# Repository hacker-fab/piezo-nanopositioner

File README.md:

# piezo-nanopositioner

To install the ESP-IDF you should follow this guide for [Linux and macOS](https://docs.espressif.com/projects/esp-idf/en/v5.2.1/esp32s3/get-started/linux-macos-setup.html) and [Windows](https://docs.espressif.com/projects/esp-idf/en/v5.2.1/esp32s3/get-started/windows-setup.html). Once you have the ESP-IDF installed you will need to run the `export.sh` file located in `esp/esp-idf/export.sh` inside the `esp` folder you setup. Once you have setup ESP-IDF for your current terminal session, you can now run `idf.py build` to compile the code or `idf.py -p {serial port the device is connected to} flash`.

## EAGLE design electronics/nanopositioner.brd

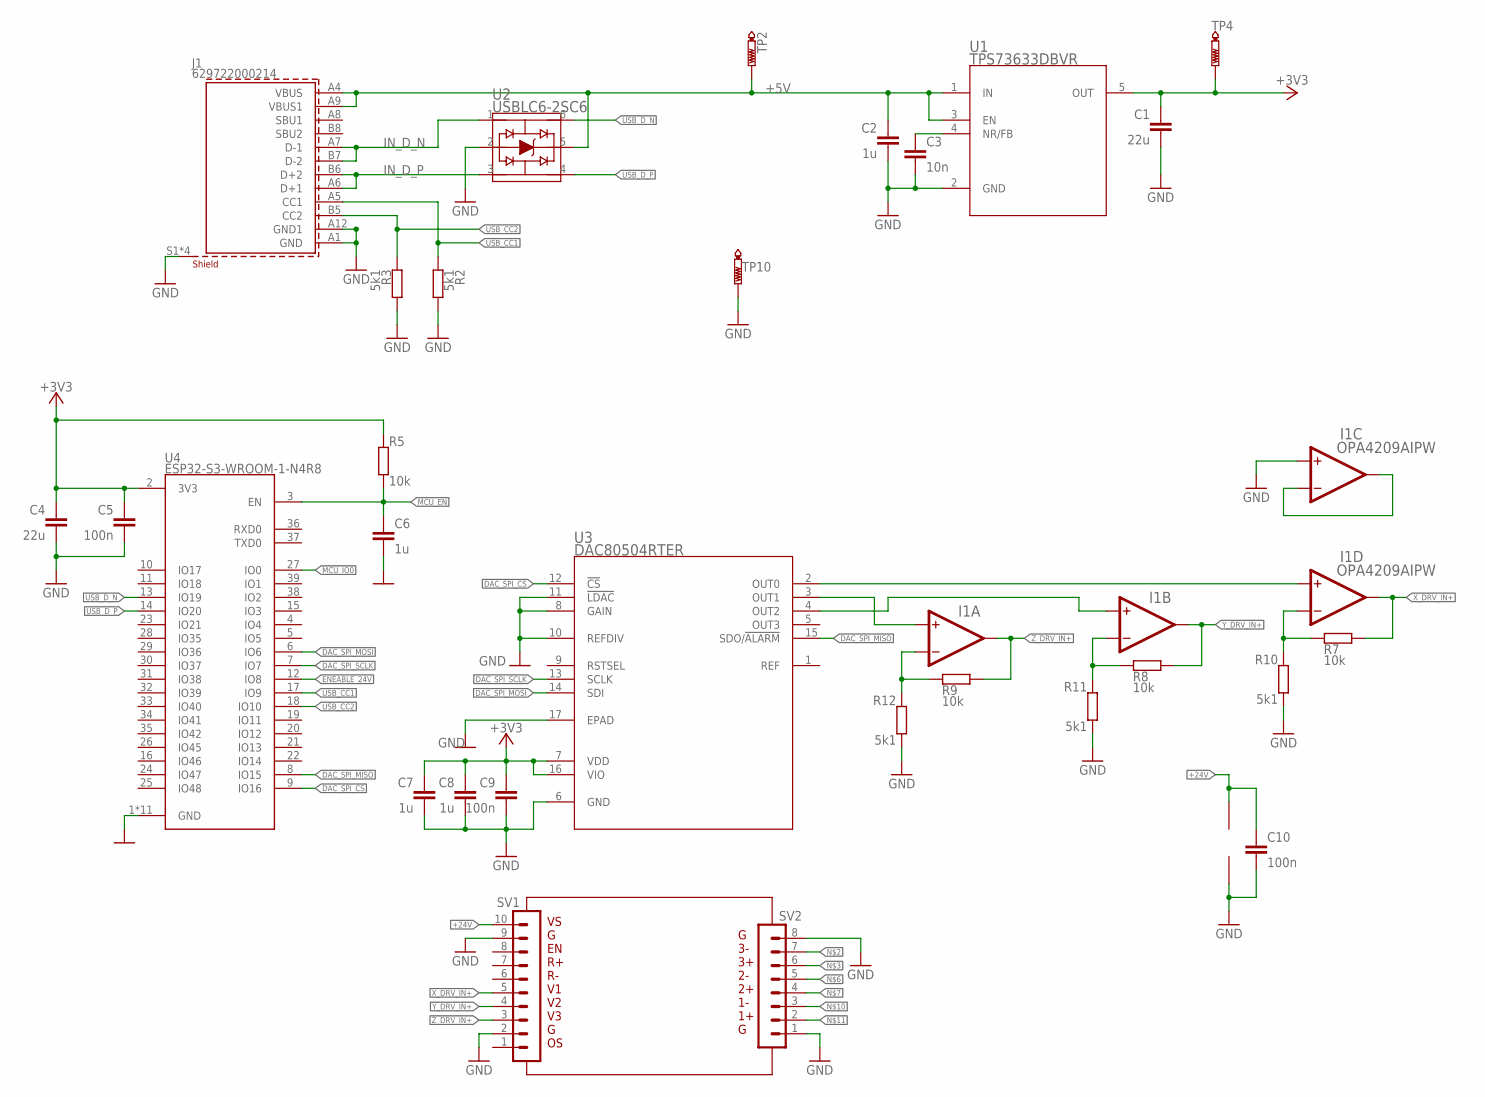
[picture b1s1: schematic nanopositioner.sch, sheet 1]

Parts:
C1, C4: 22u; C0603; MPN CL10A226MP8NUNE
C2, C6, C7, C8: 1u; C0402; MPN GRM155R61E105MA12D
C3: 10n; C0402; MPN GCM155R71H103KA55D
C5, C9, C10: 100n; C0402; MPN GRM155R71H104KE14D
I1: OPA4209AIPW; PW14; MPN OPA4209AIPW
J1: 629722000214; MPN 12402012E212A
R2, R3, R10, R11, R12: 5k1; R0402; MPN ERA-2AEB512X
R5, R7, R8, R9: 10k; R0402; MPN ERA-2AEB103X
SV1: MA10-1
SV2: MA08-1
TP2, TP4, TP10: PTR1PAD1-13; P1-13
U1: TPS73633DBVR; DBV5; MPN TPS73633DBVR
U2: USBLC6-2SC6; SOT23-6L_STM; MPN USBLC6-2SC6
U3: DAC80504RTER; RTE16_TEX; MPN DAC80504RTET
U4: ESP32-S3-WROOM-1-N4R8; XCVR_ESP32S3WROOM1N8R8; MPN ESP32-S3-WROOM-1-N4

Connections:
+3V3: C1.1, C4.1, C5.1, C7.1, C8.1, C9.1, R5.1, TP4.TP, U1.5 (OUT), U3.7 (VDD), U3.16 (VIO), U4.2 (3V3)
+5V: C2.2, J1.A4 (VBUS), J1.A9 (VBUS1), TP2.TP, U1.1 (IN), U1.3 (EN), U2.5; also elsewhere on the board
+24V: C10.1, I1.4, SV1.10; also elsewhere on the board
DAC_SPI_CS: U3.12 (!CS), U4.9 (IO16)
DAC_SPI_MISO: U3.15 (SDO/!ALARM), U4.8 (IO15)
DAC_SPI_MOSI: U3.14 (SDI), U4.6 (IO6)
DAC_SPI_SCLK: U3.13 (SCLK), U4.7 (IO7)
ENEABLE_24V: U4.12 (IO8); also elsewhere on the board
GND: C1.2, C2.1, C3.2, C4.2, C5.2, C6.1, C7.2, C8.2, C9.2, C10.2, I1.10 (INA+), I1.11, J1.A1 (GND), J1.A12 (GND1), J1.S1 (SHIELD), J1.S2 (SHIELD), J1.S3 (SHIELD), J1.S4 (SHIELD), R2.1, R3.2, R10.2, R11.2, R12.2, SV1.2, SV1.9, SV2.1, SV2.8, TP10.TP, U1.2 (GND), U2.2, U3.6 (GND), U3.8 (GAIN), U3.10 (REFDIV), U3.11 (!LDAC), U3.17 (EPAD), U4.1 (GND), U4.40 (GND), U4.41_1 (GND), U4.41_2 (GND), U4.41_3 (GND), U4.41_4 (GND), U4.41_5 (GND), U4.41_6 (GND), U4.41_7 (GND), U4.41_8 (GND), U4.41_9 (GND); also elsewhere on the board
IN_D_N: J1.A7 (D-1), J1.B7 (D-2), U2.1
IN_D_P: J1.A6 (D+1), J1.B6 (D+2), U2.3
MCU_EN: C6.2, R5.2, U4.3 (EN)
MCU_IO0: U4.27 (IO0)
unnamed: I1.13 (INA-), R7.1, R10.1
unnamed: C3.1, U1.4 (NR/FB)
unnamed: I1.3 (INA+), U3.3 (OUT1)
unnamed: I1.6 (INA-), R8.1, R11.1
unnamed: I1.5 (INA+), U3.4 (OUT2)
unnamed: I1.2 (INA-), R9.1, R12.1
unnamed: I1.12 (INA+), U3.2 (OUT0)
unnamed: I1.8 (OUTA), I1.9 (INA-)
USB_CC1: J1.A5 (CC1), R2.2, U4.17 (IO9)
USB_CC2: J1.B5 (CC2), R3.1, U4.18 (IO10)
USB_D_N: U2.6, U4.13 (IO19)
USB_D_P: U2.4, U4.14 (IO20)
X_DRV_IN+: I1.14 (OUTA), R7.2, SV1.5
Y_DRV_IN+: I1.7 (OUTA), R8.2, SV1.4
Z_DRV_IN+: I1.1 (OUTA), R9.2, SV1.3

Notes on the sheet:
VS G EN R+ R- V1 V2 V3 G OS
G 3- 3+ 2- 2+ 1- 1+ G

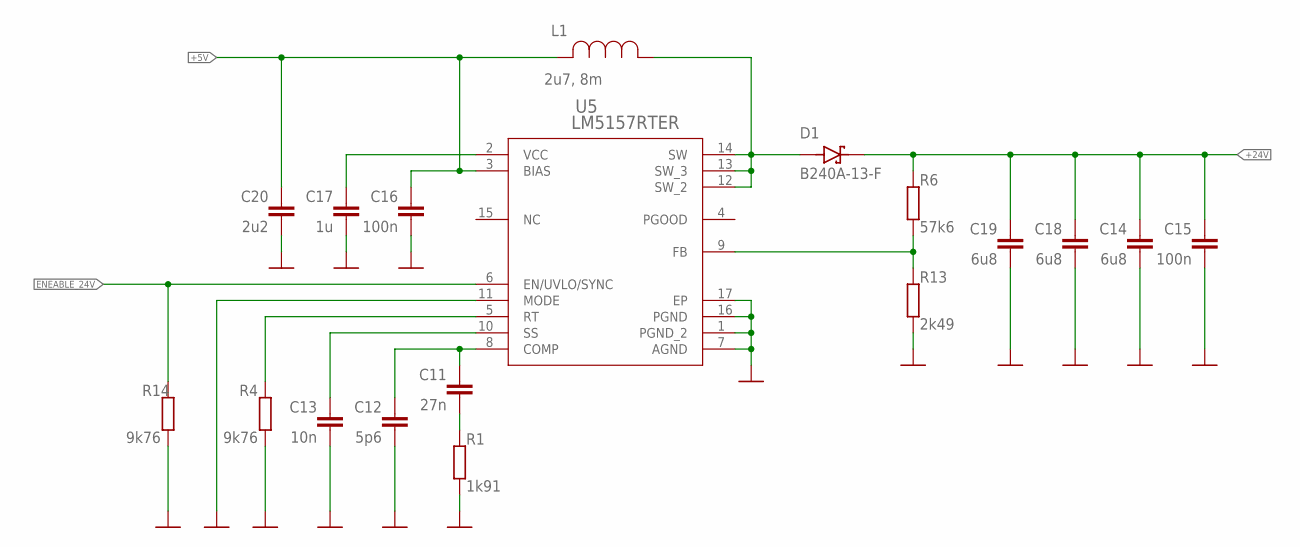
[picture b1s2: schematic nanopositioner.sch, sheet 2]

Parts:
C11: 27n; C0402; MPN GRM155R71A273KA01D
C12: 5p6; C0402; MPN GRM1555C1H5R6CA01D
C13: 10n; C0402; MPN GRM033R70J103KA01D
C14, C18, C19: 6u8; C1206; MPN C3216X5R1H685K160AB
C15: 100n; C0603; MPN CGA3E2X7R1H104K080AA
C16: 100n; C0603; MPN KGM21NR71E104KT
C17: 1u; C0402; MPN EMK107B7105KA-T
C20: 2u2; C0805; MPN GRM21BR71A225KA01L
D1: B240A-13-F; DIOM5226X230N; MPN B240A-13-F
L1: 2u7, 8m; IND_BOURNS_SDR1307; MPN SDR1307-2R7ML
R1: 1k91; R0402; MPN CRCW04021K91FKED
R4, R14: 9k76; R0402; MPN CRCW04029K76FKED
R6: 57k6; R0402; MPN CRCW040257K6FKED
R13: 2k49; R0402; MPN CRCW04022K49FKED
U5: LM5157RTER; QFN_57RTER_TEX; MPN LM5157RTER

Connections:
+5V: C16.2, C20.2, L1.2, U5.3 (BIAS); also elsewhere on the board
+24V: C14.2, C15.2, C18.2, C19.2, D1.C (K), R6.1; also elsewhere on the board
ENEABLE_24V: R14.1, U5.6 (EN/UVLO/SYNC); also elsewhere on the board
GND: C12.1, C13.1, C14.1, C15.1, C16.1, C17.1, C18.1, C19.1, C20.1, R1.2, R4.2, R13.2, R14.2, U5.1 (PGND_2), U5.7 (AGND), U5.11 (MODE), U5.16 (PGND), U5.17 (EP); also elsewhere on the board
unnamed: C11.2, C12.2, U5.8 (COMP)
unnamed: C11.1, R1.1
unnamed: C13.2, U5.10 (SS)
unnamed: R4.1, U5.5 (RT)
unnamed: D1.A, L1.1, U5.12 (SW_2), U5.13 (SW_3), U5.14 (SW)
unnamed: R6.2, R13.1, U5.9 (FB)
unnamed: C17.2, U5.2 (VCC)
PGOOD: U5.4 (PGOOD)

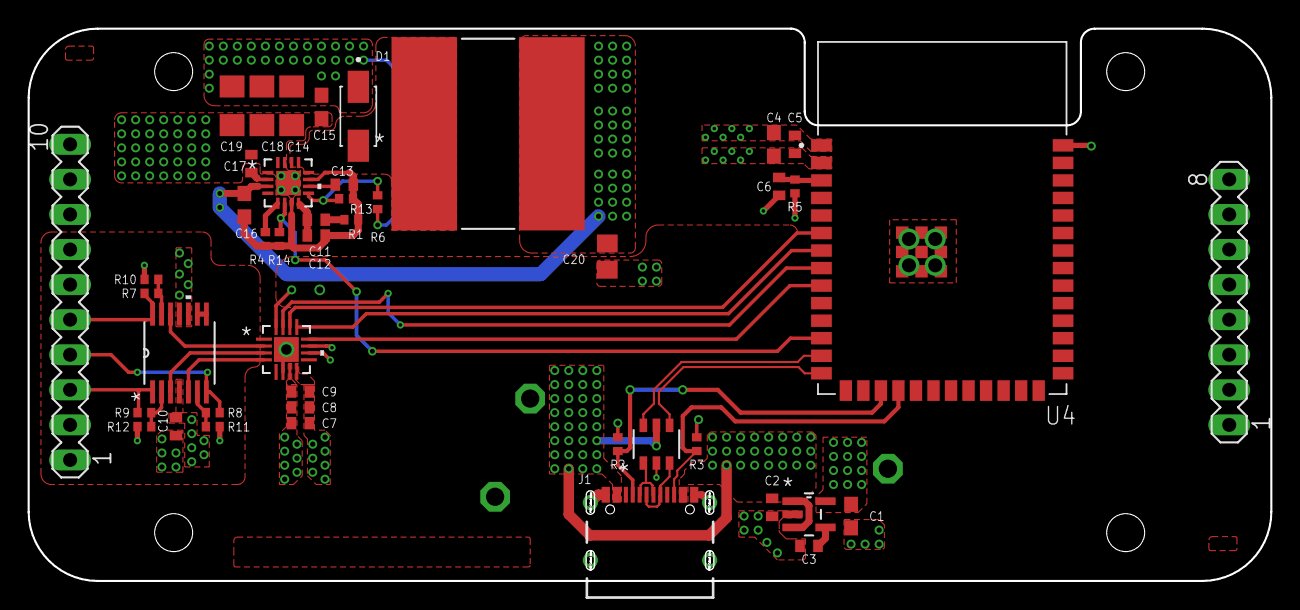
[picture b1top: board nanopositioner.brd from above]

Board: 4 copper layers, 90.0 x 40.0 mm, 48 parts (0 on the bottom side), 34 nets.

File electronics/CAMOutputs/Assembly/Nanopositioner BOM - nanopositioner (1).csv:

Qty,Designator,MPN,Description,Value,Footprint
1,SV2,,PIN HEADER,,MA08-1
1,SV1,,PIN HEADER,,MA10-1
3,"C5, C9, C10",GRM155R71H104KE14D,"CAPACITOR, European symbol",100n,C0402
1,C15,CGA3E2X7R1H104K080AA,"CAPACITOR, European symbol",100n,C0603
1,C16,KGM21NR71E104KT,"CAPACITOR, European symbol",100n,C0603
4,"R5, R7, R8, R9",ERA-2AEB103X,"RESISTOR, European symbol",10k,R0402
1,C3,GCM155R71H103KA55D,"CAPACITOR, European symbol",10n,C0402
1,C13,GRM033R70J103KA01D,"CAPACITOR, European symbol",10n,C0402
1,R1,CRCW04021K91FKED,"RESISTOR, European symbol",1k91,R0402
1,C17,EMK107B7105KA-T,"CAPACITOR, European symbol",1u,C0402
4,"C2, C6, C7, C8",GRM155R61E105MA12D,"CAPACITOR, European symbol",1u,C0402
2,"C1, C4",CL10A226MP8NUNE,"CAPACITOR, European symbol",22u,C0603
1,C11,GRM155R71A273KA01D,"CAPACITOR, European symbol",27n,C0402
1,R13,CRCW04022K49FKED,"RESISTOR, European symbol",2k49,R0402
1,C20,GRM21BR71A225KA01L,"CAPACITOR, European symbol",2u2,C0805
1,L1,SDR1307-2R7ML,,"2u7, 8m",IND_BOURNS_SDR1307
1,R6,CRCW040257K6FKED,"RESISTOR, European symbol",57k6,R0402
5,"R2, R3, R10, R11, R12",ERA-2AEB512X,"RESISTOR, European symbol",5k1,R0402
1,C12,GRM1555C1H5R6CA01D,"CAPACITOR, European symbol",5p6,C0402
1,J1,12402012E212A,WR-COM USB 2.0 Type C Plug Vertical SMT,629722000214,629722000214
3,"C14, C18, C19",C3216X5R1H685K160AB,"CAPACITOR, European symbol",6u8,C1206
2,"R4, R14",CRCW04029K76FKED,"RESISTOR, European symbol",9k76,R0402
1,D1,B240A-13-F,Diode Schottky 40V 2A Surface Mount SMA,B240A-13-F,DIOM5226X230N
1,U3,DAC80504RTET,,DAC80504RTER,RTE16_TEX
1,U4,ESP32-S3-WROOM-1-N4,Check availability  Check availability,ESP32-S3-WROOM-1-N4R8,XCVR_ESP32S3WROOM1N8R8
1,U5,LM5157RTER,,LM5157RTER,QFN_57RTER_TEX
1,I1,OPA4209AIPW,,OPA4209AIPW,PW14
3,"TP2, TP4, TP10",,TEST PIN,PTR1PAD1-13,P1-13
1,U1,TPS73633DBVR,,TPS73633DBVR,DBV5
1,U2,USBLC6-2SC6,,USBLC6-2SC6,SOT23-6L_STM

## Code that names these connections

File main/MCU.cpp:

#include "driver/spi_common.h"
#include "driver/spi_master.h"
#include "driver/uart.h"
#include "esp_err.h"
#include "esp_system.h"
#include "freertos/FreeRTOS.h"
#include "freertos/portmacro.h"
#include "freertos/task.h"
#include "driver/gpio.h"
#include "hal/gpio_types.h"
#include <stdint.h>
#include <sys/_stdint.h>
#include <sys/errno.h>
#include <sys/types.h>
#include <string.h>
#include <math.h>
#include <string>
#include "esp_timer.h"
#include "hal/usb_phy_types.h"
#include "tinyusb.h"
#include "tusb_cdc_acm.h"
#include "tusb_console.h"

const gpio_num_t ENEABLE_24V_PIN = GPIO_NUM_8;
const gpio_num_t DAC_SPI_MOSI = GPIO_NUM_6;
const gpio_num_t DAC_SPI_MISO = GPIO_NUM_15;
const gpio_num_t DAC_SPI_SCLK = GPIO_NUM_7;
const gpio_num_t DAC_SPI_CS = GPIO_NUM_16;

const int railCorrection = 12000;
const int maxADCValue = pow(2, 16)-1-railCorrection;

int g_itf;
int driveFrequency = 1000;
uint8_t transactionBuffer[CONFIG_TINYUSB_CDC_RX_BUFSIZE + 1] = {0};

int isDriverOn = 0;
int safeToRun = 1;
int running = 0;
spi_device_handle_t SPIDevice;

enum DACRegister : uint8_t {
	NOP = 0x00,
	DEVICEID = 0x01,
	SYNC = 0x02,
	CONFIG = 0x02,
	GAIN = 0x04,
	TRIGGER = 0x05,
	BRDCAST = 0x06,
	STATUS = 0x07,
	DAC0VAl = 0x08,
	DAC1VAl = 0x09,
	DAC2VAL = 0x0A,
	DAC3VAL = 0x0B,
};

enum DACChannel : uint8_t {
	DAC0 = 0,
	DAC1 = 1,
	DAC2 = 2,
	DAC3 = 3,
};

enum USBOpCode : uint32_t {
	ABORT = 0x74726261, // abrt
	RUN = 0x706E7572, // runp
	SETCH = 0x63746573, // setc
	SETFREQ = 0x66746573, // setf
};

void turnDriver(uint32_t on) {
	gpio_set_level(ENEABLE_24V_PIN, on);
}

void setupPins() {
	gpio_set_direction(ENEABLE_24V_PIN, GPIO_MODE_OUTPUT);
}

void initiateSPI(){

	spi_bus_config_t buscfg = {
		.mosi_io_num = DAC_SPI_MOSI,
		.miso_io_num = DAC_SPI_MISO,
		.sclk_io_num = DAC_SPI_SCLK,
		.max_transfer_sz = 4092,
	};

	spi_device_interface_config_t devcfg = {
		.command_bits = 0,
		.address_bits = 0,
		.dummy_bits = 0,
		.mode = 1,
		.clock_source = SPI_CLK_SRC_DEFAULT,
		.cs_ena_pretrans = 0,
		.cs_ena_posttrans = 0,
		.clock_speed_hz = SPI_MASTER_FREQ_40M,
		.spics_io_num = DAC_SPI_CS,
		.queue_size = 7,
	};

	esp_err_t ret;

	ret = spi_bus_initialize(SPI2_HOST, &buscfg, SPI_DMA_DISABLED);
	assert(ret==ESP_OK);

	ret = spi_bus_add_device(SPI2_HOST, &devcfg, &SPIDevice);
	assert(ret==ESP_OK);

	vTaskDelay(100 / portTICK_PERIOD_MS);
}

void writeToRegister(DACRegister address, uint16_t value)    {
	spi_device_acquire_bus(SPIDevice, portMAX_DELAY);
	spi_transaction_t transaction = {
		.flags = SPI_TRANS_USE_TXDATA,
		.length = 3*8,
	};

	transaction.tx_data[0] = (0b00000000 + (uint8_t)address);
	transaction.tx_data[1] = value >> 8;
	transaction.tx_data[2] = value;

	esp_err_t ret;
	ret = spi_device_transmit(SPIDevice, &transaction);
	assert(ret==ESP_OK);
	spi_device_release_bus(SPIDevice);
}

void fast_writeToRegister(DACRegister address, uint16_t value)    {
	spi_transaction_t transaction = {
		.flags = SPI_TRANS_USE_TXDATA,
		.length = 3*8,
	};

	transaction.tx_data[0] = (0b00000000 + (uint8_t)address);
	transaction.tx_data[1] = value >> 8;
	transaction.tx_data[2] = value;

	spi_device_polling_transmit(SPIDevice, &transaction);
}

void readFromRegister(DACRegister address, uint16_t &value){
	spi_device_acquire_bus(SPIDevice, portMAX_DELAY);
	uint8_t t_bytes[3];
	t_bytes[0] = (0b10000000 + (uint8_t)address);
	t_bytes[1] = 0;
	t_bytes[2] = 0;

	uint8_t r_bytes[3];
	memset(r_bytes, 0, sizeof(r_bytes));

	spi_transaction_t transaction = {
		.length = sizeof(t_bytes)*8,    // length in bits
		.tx_buffer = t_bytes,
		.rx_buffer = r_bytes
	};

	esp_err_t ret;
	ret = spi_device_transmit(SPIDevice, &transaction);
	assert(ret==ESP_OK);

	memset(r_bytes, 0, sizeof(r_bytes));

	transaction = {
		.length = sizeof(r_bytes)*8,    // length in bits
		.tx_buffer = r_bytes,
		.rx_buffer = r_bytes
	};

	ret = spi_device_transmit(SPIDevice, &transaction);
	assert(ret==ESP_OK);

	value = (uint16_t)(r_bytes[1] << 8 | r_bytes[2]);
	spi_device_release_bus(SPIDevice);
}

void setChannelBroadcast(DACChannel channel, int broadcast) {
	uint16_t registerValue = 0;
	readFromRegister(DACRegister::SYNC, registerValue);

	if(broadcast)
		writeToRegister(DACRegister::SYNC, registerValue | (1 << (8+channel)));
	else
		writeToRegister(DACRegister::SYNC, registerValue & (1 << (8+channel)));
}

void broadcast(uint16_t value) {
	writeToRegister(DACRegister::BRDCAST, value);
}

void fast_broadcast(uint16_t value) {
	fast_writeToRegister(DACRegister::BRDCAST, value+railCorrection);
}

long map(long x, long in_min, long in_max, long out_min, long out_max) {
    return (x - in_min) * (out_max - out_min) / (in_max - in_min) + out_min;
}

void stickSlip(int frequency, int direction) {
  long usPeriod = 1000000 / frequency;
  uint64_t usStart = esp_timer_get_time();
	uint64_t now = esp_timer_get_time();

	fast_broadcast(direction ? 0 : maxADCValue);

  while (1) {
		now = esp_timer_get_time();
		if (now - usStart > usPeriod) break;
		if (!safeToRun) return;

		if (direction == 1) {
			fast_broadcast((double)maxADCValue * pow((double)(now - usStart) / (double)usPeriod, 2));
		} else {
			fast_broadcast(maxADCValue - (double)maxADCValue * pow((double)(now - usStart) / (double)usPeriod, 2));
		}
	}

	fast_broadcast(0);
}

void initiateDAC() {
	setChannelBroadcast(DACChannel::DAC0, 0);
	setChannelBroadcast(DACChannel::DAC1, 0);
	setChannelBroadcast(DACChannel::DAC2, 0);
	setChannelBroadcast(DACChannel::DAC3, 0);

	writeToRegister(DACRegister::GAIN, 0b0000000100001111);
}

bool startsWithOpcode(int msgSize, USBOpCode opCode) {
	if(msgSize<sizeof(opCode))
		return 0;
	
	return memcmp(transactionBuffer, &opCode, sizeof(opCode)) == 0;
}

bool bufferContentIsBool(int i) {
	if(transactionBuffer[i]<48 || transactionBuffer[i]>48+1) return 0;
	
	return 1;
}

bool bufferContentIsNumber(int i) {
	if(transactionBuffer[i]<48 || transactionBuffer[i]>57) return 0;
	
	return 1;
}

void USBHandler(int msgSize) {
	if(startsWithOpcode(msgSize, USBOpCode::ABORT)) {
		safeToRun=0;
		running=0;

		tinyusb_cdcacm_write_queue((tinyusb_cdcacm_itf_t)g_itf, transactionBuffer, 4);
		tinyusb_cdcacm_write_flush((tinyusb_cdcacm_itf_t)g_itf, 0);

		return;
	}

	if(running) return;
	safeToRun=1;

	if(startsWithOpcode(msgSize, USBOpCode::SETCH)) {
		if(msgSize<7) return;

		for(int i=0; i<3; i++) {
			if(!bufferContentIsBool(4+i)) return;
		}

		setChannelBroadcast(DACChannel::DAC0, transactionBuffer[4]-48);
		setChannelBroadcast(DACChannel::DAC1, transactionBuffer[5]-48);
		setChannelBroadcast(DACChannel::DAC2, transactionBuffer[6]-48);

		tinyusb_cdcacm_write_queue((tinyusb_cdcacm_itf_t)g_itf, transactionBuffer, 4);
		tinyusb_cdcacm_write_flush((tinyusb_cdcacm_itf_t)g_itf, 0);

		return;
	}

	if(startsWithOpcode(msgSize, USBOpCode::SETFREQ)) {
		if(msgSize<9) return;

		for(int i=0; i<5; i++) {
			if(!bufferContentIsNumber(4+i)) return;
		}
		std::string n(transactionBuffer+4, transactionBuffer+4+5);
		driveFrequency = std::stoi(n);

		tinyusb_cdcacm_write_queue((tinyusb_cdcacm_itf_t)g_itf, transactionBuffer, 4);
		tinyusb_cdcacm_write_flush((tinyusb_cdcacm_itf_t)g_itf, 0);

		return;
	}

	if(startsWithOpcode(msgSize, USBOpCode::RUN)) {
		if(msgSize<7) return;

		if(!bufferContentIsBool(4)) return;

		for(int i=0; i<2; i++) {
			if(!bufferContentIsNumber(4+i)) return;
		}

		running=1;

		std::string n(transactionBuffer+5, transactionBuffer+5+2);
		int usDuration = std::stoi(n) * 1000000;

		spi_device_acquire_bus(SPIDevice, portMAX_DELAY);

		uint64_t yieldTimer = esp_timer_get_time();
		uint64_t usStart = yieldTimer;
		while(esp_timer_get_time() - usStart < usDuration) {
			if (esp_timer_get_time() - yieldTimer > 10000000) {
				vPortYield(); // yield
				yieldTimer = esp_timer_get_time();
			}

			if(!safeToRun) {
				safeToRun=1;
				return;
			}

			stickSlip(driveFrequency, transactionBuffer[4]-48);
		}
		spi_device_release_bus(SPIDevice);

		running=0;

		tinyusb_cdcacm_write_queue((tinyusb_cdcacm_itf_t)g_itf, transactionBuffer, 4);
		tinyusb_cdcacm_write_flush((tinyusb_cdcacm_itf_t)g_itf, 0);

		return;
	}

}

void tinyusb_cdc_rx_callback(int itf, cdcacm_event_t *event) {
	size_t rx_size = 0;

	tinyusb_cdcacm_read((tinyusb_cdcacm_itf_t)itf, transactionBuffer, CONFIG_TINYUSB_CDC_RX_BUFSIZE, &rx_size);
	if(rx_size > 0){
		g_itf = itf;

		USBHandler(rx_size);
	}
}

void initiateUSB() {
		const tinyusb_config_t tusb_cfg = {
		.device_descriptor = NULL,
		.string_descriptor = NULL,
		.external_phy = false,
		.configuration_descriptor = NULL,
	};

	ESP_ERROR_CHECK(tinyusb_driver_install(&tusb_cfg));

	tinyusb_config_cdcacm_t acm_cfg;
	memset(&acm_cfg, 0, sizeof(acm_cfg));
	acm_cfg.callback_rx = &tinyusb_cdc_rx_callback;

	ESP_ERROR_CHECK(tusb_cdc_acm_init(&acm_cfg));

	esp_tusb_init_console(TINYUSB_CDC_ACM_0);
}

extern "C" void app_main(void) {
	setupPins();
	turnDriver(1);
	
	initiateSPI();
	initiateDAC();
	initiateUSB();
}

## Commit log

2024-03-24 start
2024-03-24 readme

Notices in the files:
parts and their libraries:
Eagle_WR-USB: Copyright: Würth Elektronik
COPYRIGHT: Copyright (C) 2024 Ultra Librarian. All rights reserved.
COPYRIGHT: Copyright (C) 2023 Ultra Librarian. All rights reserved.
